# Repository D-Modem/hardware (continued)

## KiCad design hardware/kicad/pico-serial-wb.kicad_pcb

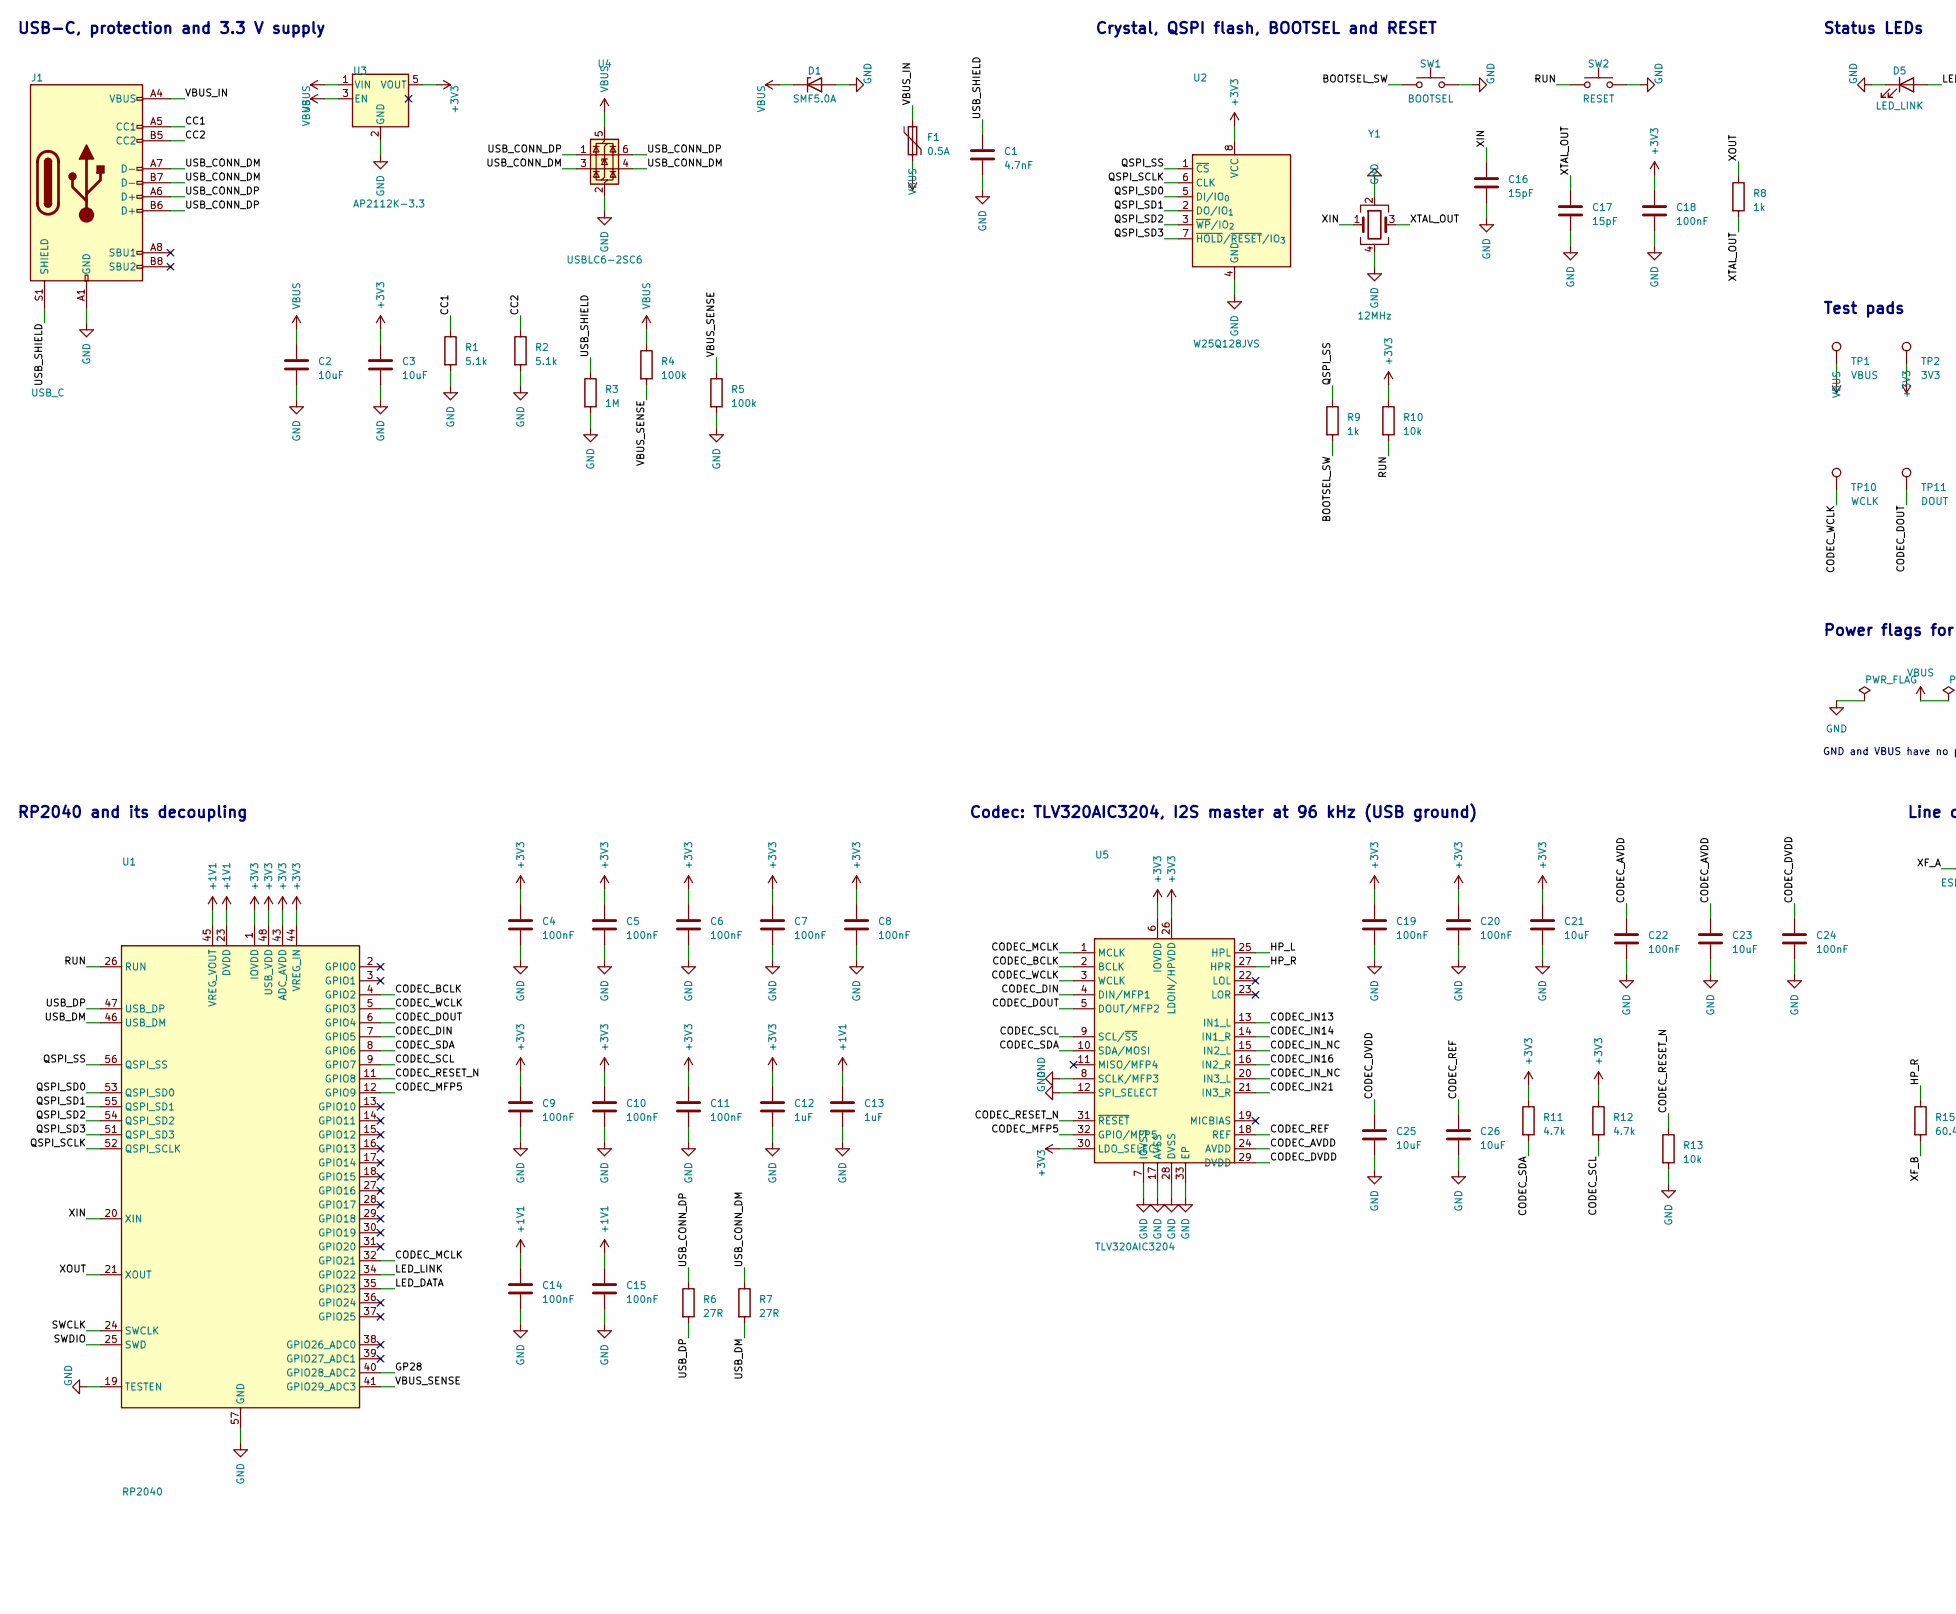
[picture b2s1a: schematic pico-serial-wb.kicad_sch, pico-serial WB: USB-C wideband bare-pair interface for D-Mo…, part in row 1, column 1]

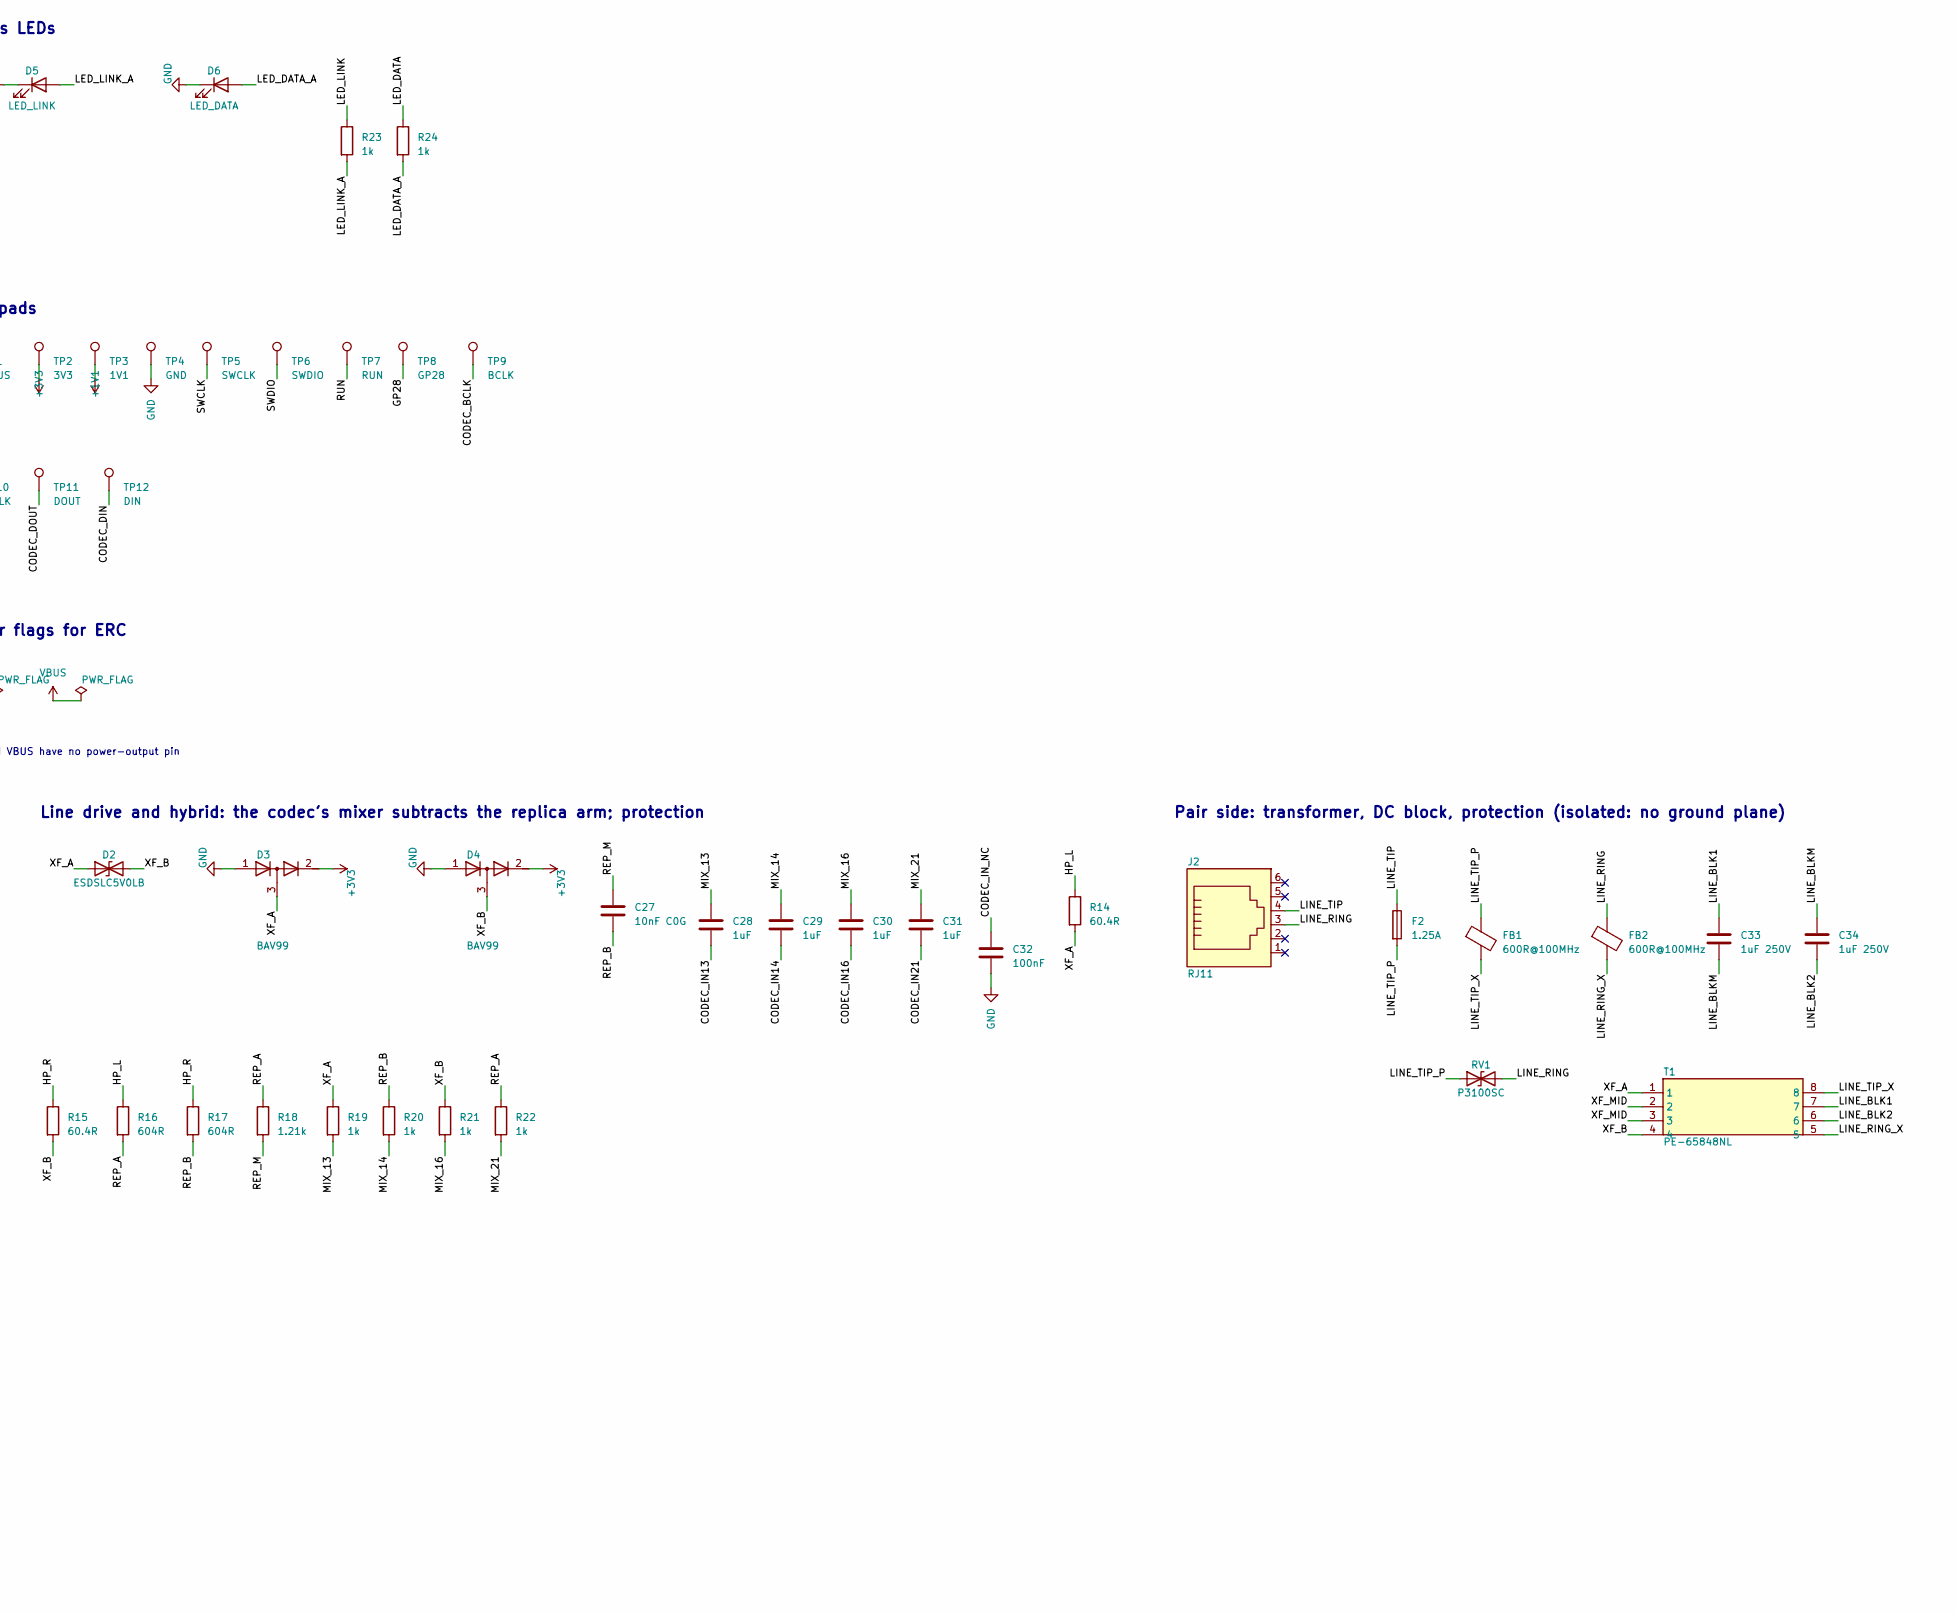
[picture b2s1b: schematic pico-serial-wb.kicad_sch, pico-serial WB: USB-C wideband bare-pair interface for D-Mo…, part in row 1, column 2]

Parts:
C1: 4.7nF; C_0402_1005Metric; LCSC C1538
C2, C3, C21, C23, C25, C26: 10uF; C_0603_1608Metric; LCSC C19702
C4, C5, C6, C7, C8, C9, C10, C11, C14, C15, C18, C19, C20, C22, C24, C32: 100nF; C_0402_1005Metric; LCSC C1525
C12, C13, C28, C29, C30, C31: 1uF; C_0402_1005Metric; LCSC C52923
C16, C17: 15pF; C_0402_1005Metric; LCSC C1548
C27: 10nF C0G; C_0805_2012Metric; LCSC C2971995
C33, C34: 1uF 250V; C_1812_4532Metric; LCSC C381468
D1: SMF5.0A; D_SOD-123F; LCSC C151296
D2: ESDSLC5V0LB; D_0402_1005Metric; LCSC C2762104
D3, D4: BAV99; SOT-23; LCSC C2500
D5: LED_LINK; LED_0603_1608Metric; LCSC C2286
D6: LED_DATA; LED_0603_1608Metric; LCSC C2286
F1: 0.5A; Fuse_1206_3216Metric; LCSC C163512
F2: 1.25A; Fuse_Littelfuse_0461; LCSC C99554
FB1, FB2: 600R@100MHz; L_0603_1608Metric; LCSC C19330
J1: USB_C; USB_C_Receptacle_HRO_TYPE-C-31-M-12; LCSC C165948
J2: RJ11; RJ11_Ckmtw_R-RJ11R06P-A800; LCSC C189750
R1, R2: 5.1k; R_0402_1005Metric; LCSC C25905
R3: 1M; R_0402_1005Metric; LCSC C26083
R4, R5: 100k; R_0402_1005Metric; LCSC C25741
R6, R7: 27R; R_0402_1005Metric; LCSC C25100
R8, R9, R19, R20, R21, R22, R23, R24: 1k; R_0402_1005Metric; LCSC C11702
R10, R13: 10k; R_0402_1005Metric; LCSC C25744
R11, R12: 4.7k; R_0402_1005Metric; LCSC C25900
R14, R15: 60.4R; R_0603_1608Metric; LCSC C2933247
R16, R17: 604R; R_0603_1608Metric; LCSC C32183
R18: 1.21k; R_0603_1608Metric; LCSC C22835
RV1: P3100SC; D_SMB; LCSC C151191
SW1: BOOTSEL; SW_SPST_TS-1088-xR020; LCSC C720477
SW2: RESET; SW_SPST_TS-1088-xR020; LCSC C720477
T1: PE-65848NL; Pulse_PE-65848; LCSC C7261159
TP1: VBUS; TestPoint_Pad_D1.0mm
TP2: 3V3; TestPoint_Pad_D1.0mm
TP3: 1V1; TestPoint_Pad_D1.0mm
TP4: GND; TestPoint_Pad_D1.0mm
TP5: SWCLK; TestPoint_Pad_D1.0mm
TP6: SWDIO; TestPoint_Pad_D1.0mm
TP7: RUN; TestPoint_Pad_D1.0mm
TP8: GP28; TestPoint_Pad_D1.0mm
TP9: BCLK; TestPoint_Pad_D1.0mm
TP10: WCLK; TestPoint_Pad_D1.0mm
TP11: DOUT; TestPoint_Pad_D1.0mm
TP12: DIN; TestPoint_Pad_D1.0mm
U1: RP2040; QFN-56-1EP_7x7mm_P0.4mm_EP3.2x3.2mm; LCSC C2040
U2: W25Q128JVS; SOIC-8_5.3x5.3mm_P1.27mm; LCSC C97521
U3: AP2112K-3.3; SOT-23-5; LCSC C51118
U4: USBLC6-2SC6; SOT-23-6; LCSC C7519
U5: TLV320AIC3204; QFN-32-1EP_5x5mm_P0.5mm_EP3.45x3.45mm; LCSC C24109
Y1: 12MHz; Crystal_SMD_3225-4Pin_3.2x2.5mm; LCSC C20625731

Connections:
+1V1: C13.1, C14.1, C15.1, TP3.1, U1.23 (DVDD), U1.45 (VREG_VOUT), U1.50 (DVDD)
+3V3: C3.1, C4.1, C5.1, C6.1, C7.1, C8.1, C9.1, C10.1, C11.1, C12.1, C18.1, C19.1, C20.1, C21.1, D3.2 (K), D4.2 (K), R10.1, R11.1, R12.1, TP2.1, U1.1 (IOVDD), U1.10 (IOVDD), U1.22 (IOVDD), U1.33 (IOVDD), U1.42 (IOVDD), U1.43 (ADC_AVDD), U1.44 (VREG_IN), U1.48 (USB_VDD), U1.49 (IOVDD), U2.8 (VCC), U3.5 (VOUT), U5.6 (IOVDD), U5.26 (LDOIN/HPVDD), U5.30 (LDO_SELECT)
/BOOTSEL_SW: R9.2, SW1.1
/CC1: J1.A5 (CC1), R1.1
/CC2: J1.B5 (CC2), R2.1
/CODEC_AVDD: C22.1, C23.1, U5.24 (AVDD)
/CODEC_BCLK: TP9.1, U1.4 (GPIO2), U5.2 (BCLK)
/CODEC_DIN: TP12.1, U1.7 (GPIO5), U5.4 (DIN/MFP1)
/CODEC_DOUT: TP11.1, U1.6 (GPIO4), U5.5 (DOUT/MFP2)
/CODEC_DVDD: C24.1, C25.1, U5.29 (DVDD)
/CODEC_IN13: C28.2, U5.13 (IN1_L)
/CODEC_IN14: C29.2, U5.14 (IN1_R)
/CODEC_IN16: C30.2, U5.16 (IN2_R)
/CODEC_IN21: C31.2, U5.21 (IN3_R)
/CODEC_IN_NC: C32.1, U5.15 (IN2_L), U5.20 (IN3_L)
/CODEC_MCLK: U1.32 (GPIO21), U5.1 (MCLK)
/CODEC_MFP5: U1.12 (GPIO9), U5.32 (GPIO/MFP5)
/CODEC_REF: C26.1, U5.18 (REF)
/CODEC_RESET_N: R13.1, U1.11 (GPIO8), U5.31 (~RESET)
/CODEC_SCL: R12.2, U1.9 (GPIO7), U5.9 (SCL/~SS)
/CODEC_SDA: R11.2, U1.8 (GPIO6), U5.10 (SDA/MOSI)
/CODEC_WCLK: TP10.1, U1.5 (GPIO3), U5.3 (WCLK)
/GP28: TP8.1, U1.40 (GPIO28_ADC2)
/HP_L: R14.1, R16.1, U5.25 (HPL)
/HP_R: R15.1, R17.1, U5.27 (HPR)
/LED_DATA: R24.1, U1.35 (GPIO23)
/LED_DATA_A: D6.2 (A), R24.2
/LED_LINK: R23.1, U1.34 (GPIO22)
/LED_LINK_A: D5.2 (A), R23.2
/LINE_BLK1: C33.1, T1.7
/LINE_BLK2: C34.2, T1.6
/LINE_BLKM: C33.2, C34.1
/LINE_RING: FB2.1, J2.3, RV1.2 (A2)
/LINE_RING_X: FB2.2, T1.5
/LINE_TIP: F2.1, J2.4
/LINE_TIP_P: F2.2, FB1.1, RV1.1 (A1)
/LINE_TIP_X: FB1.2, T1.8
/MIX_13: C28.1, R19.2
/MIX_14: C29.1, R20.2
/MIX_16: C30.1, R21.2
/MIX_21: C31.1, R22.2
/QSPI_SCLK: U1.52 (QSPI_SCLK), U2.6 (CLK)
/QSPI_SD0: U1.53 (QSPI_SD0), U2.5 (DI/IO_{0})
/QSPI_SD1: U1.55 (QSPI_SD1), U2.2 (DO/IO_{1})
/QSPI_SD2: U1.54 (QSPI_SD2), U2.3 (~WP/IO_{2})
/QSPI_SD3: U1.51 (QSPI_SD3), U2.7 (~HOLD/~RESET/IO_{3})
/QSPI_SS: R9.1, U1.56 (QSPI_SS), U2.1 (~CS)
/REP_A: R16.2, R18.1, R22.1
/REP_B: C27.2, R17.2, R20.1
/REP_M: C27.1, R18.2
/RUN: R10.2, SW2.1, TP7.1, U1.26 (RUN)
/SWCLK: TP5.1, U1.24 (SWCLK)
/SWDIO: TP6.1, U1.25 (SWD)
/USB_CONN_DM: J1.A7 (D-), J1.B7 (D-), R7.1, U4.3 (I/O2), U4.4 (I/O2)
/USB_CONN_DP: J1.A6 (D+), J1.B6 (D+), R6.1, U4.1 (I/O1), U4.6 (I/O1)
/USB_DM: R7.2, U1.46 (USB_DM)
/USB_DP: R6.2, U1.47 (USB_DP)
/USB_SHIELD: C1.1, J1.S1 (SHIELD), R3.1
/VBUS_IN: F1.1, J1.A4 (VBUS), J1.A9 (VBUS), J1.B4 (VBUS), J1.B9 (VBUS)
/VBUS_SENSE: R4.2, R5.1, U1.41 (GPIO29_ADC3)
/XF_A: D2.1 (A1), D3.3 (common), R14.2, R19.1, T1.1
/XF_B: D2.2 (A2), D4.3 (common), R15.2, R21.1, T1.4
/XF_MID: T1.2, T1.3
/XIN: C16.1, U1.20 (XIN), Y1.1
/XOUT: R8.1, U1.21 (XOUT)
/XTAL_OUT: C17.1, R8.2, Y1.3
GND: C1.2, C2.2, C3.2, C4.2, C5.2, C6.2, C7.2, C8.2, C9.2, C10.2, C11.2, C12.2, C13.2, C14.2, C15.2, C16.2, C17.2, C18.2, C19.2, C20.2, C21.2, C22.2, C23.2, C24.2, C25.2, C26.2, C32.2, D1.2 (A), D3.1 (A), D4.1 (A), D5.1 (K), D6.1 (K), J1.A1 (GND), J1.A12 (GND), J1.B1 (GND), J1.B12 (GND), R1.2, R2.2, R3.2, R5.2, R13.2, SW1.2, SW2.2, TP4.1, U1.19 (TESTEN), U1.57 (GND), U2.4 (GND), U3.2 (GND), U4.2 (GND), U5.7 (IOVSS), U5.8 (SCLK/MFP3), U5.12 (SPI_SELECT), U5.17 (AVSS), U5.28 (DVSS), U5.33 (EP), Y1.2, Y1.4
VBUS: C2.1, D1.1 (K), F1.2, R4.1, TP1.1, U3.1 (VIN), U3.3 (EN), U4.5 (VBUS)

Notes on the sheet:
GND and VBUS have no power-output pin
USB-C, protection and 3.3 V supply
Crystal, QSPI flash, BOOTSEL and RESET
Status LEDs
Test pads
Power flags for ERC
RP2040 and its decoupling
Codec: TLV320AIC3204, I2S master at 96 kHz (USB ground)
Line drive and hybrid: the codec's mixer subtracts the replica arm; protection
Pair side: transformer, DC block, protection (isolated: no ground plane)
Generated by hardware/kicad/build_schematic.py from hardware/netlist/build_netlist.py. Edit the netlist script and regenerate; hand edits here are lost.

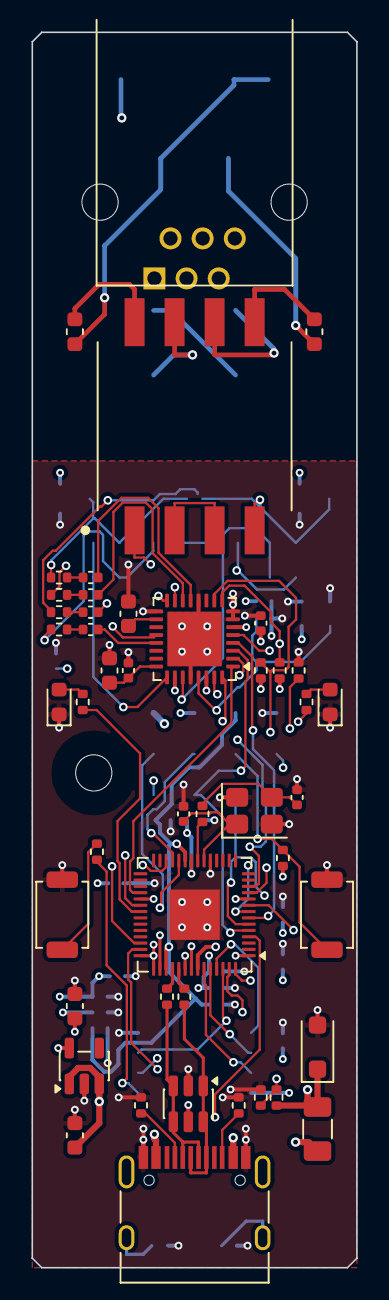
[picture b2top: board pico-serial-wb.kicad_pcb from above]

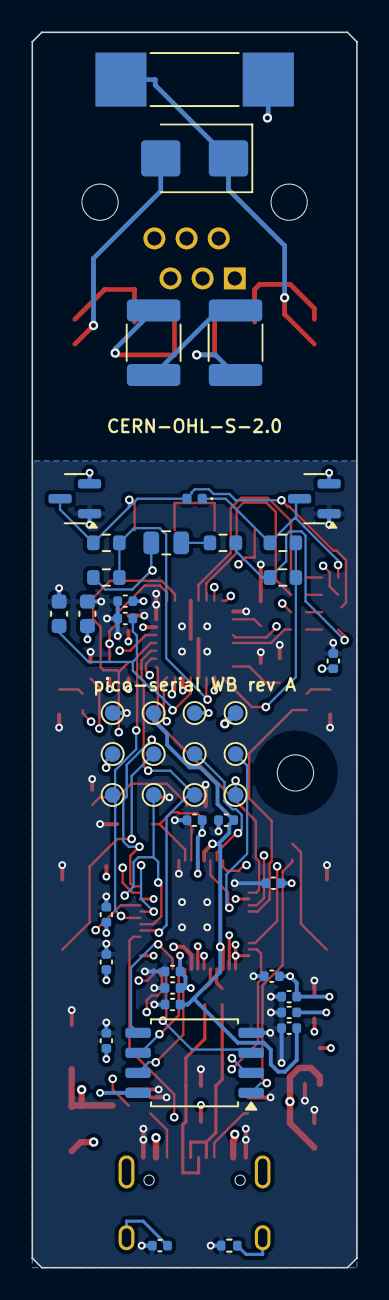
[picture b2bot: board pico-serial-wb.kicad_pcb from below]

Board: 4 copper layers, 20.6 x 78.4 mm, 93 parts (46 on the bottom side), 68 nets.

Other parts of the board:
H1: M2 screw; MountingHole_M2

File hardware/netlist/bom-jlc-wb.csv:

Comment,Designator,Footprint,LCSC Part #
4.7nF,"C1",C_0402_1005Metric,C1538
10uF,"C2,C3,C21,C23,C25,C26",C_0603_1608Metric,C19702
100nF,"C4,C5,C6,C7,C8,C9,C10,C11,C14,C15,C18,C19,C20,C22,C24,C32",C_0402_1005Metric,C1525
1uF,"C12,C13,C28,C29,C30,C31",C_0402_1005Metric,C52923
15pF,"C16,C17",C_0402_1005Metric,C1548
10nF C0G,"C27",C_0805_2012Metric,C2971995
1uF 250V,"C33,C34",C_1812_4532Metric,C381468
SMF5.0A,"D1",D_SOD-123F,C151296
ESDSLC5V0LB,"D2",D_0402_1005Metric,C2762104
BAV99,"D3,D4",SOT-23,C2500
LED_LINK,"D5",LED_0603_1608Metric,C2286
LED_DATA,"D6",LED_0603_1608Metric,C2286
0.5A,"F1",Fuse_1206_3216Metric,C163512
1.25A,"F2",Fuse_Littelfuse_0461,C99554
600R@100MHz,"FB1,FB2",L_0603_1608Metric,C19330
USB_C,"J1",USB_C_Receptacle_HRO_TYPE-C-31-M-12,C165948
5.1k,"R1,R2",R_0402_1005Metric,C25905
1M,"R3",R_0402_1005Metric,C26083
100k,"R4,R5",R_0402_1005Metric,C25741
27R,"R6,R7",R_0402_1005Metric,C25100
1k,"R8,R9,R19,R20,R21,R22,R23,R24",R_0402_1005Metric,C11702
10k,"R10,R13",R_0402_1005Metric,C25744
4.7k,"R11,R12",R_0402_1005Metric,C25900
60.4R,"R14,R15",R_0603_1608Metric,C2933247
604R,"R16,R17",R_0603_1608Metric,C32183
1.21k,"R18",R_0603_1608Metric,C22835
P3100SC,"RV1",D_SMB,C151191
BOOTSEL,"SW1",SW_SPST_TS-1088-xR020,C720477
RESET,"SW2",SW_SPST_TS-1088-xR020,C720477
PE-65848NL,"T1",Pulse_PE-65848,C7261159
RP2040,"U1",QFN-56-1EP_7x7mm_P0.4mm_EP3.2x3.2mm,C2040
W25Q128JVS,"U2",SOIC-8_5.3x5.3mm_P1.27mm,C97521
AP2112K-3.3,"U3",SOT-23-5,C51118
USBLC6-2SC6,"U4",SOT-23-6,C7519
TLV320AIC3204,"U5",QFN-32-1EP_5x5mm_P0.5mm_EP3.45x3.45mm,C24109
12MHz,"Y1",Crystal_SMD_3225-4Pin_3.2x2.5mm,C20625731

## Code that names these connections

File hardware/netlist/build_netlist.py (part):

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P, PI, PO, I, O, B, NC = "passive", "power_in", "power_out", "input", "output", "bidirectional", "no_connect"

RP2040 = {
    "1": ("IOVDD", PI), "2": ("GPIO0", B), "3": ("GPIO1", B), "4": ("GPIO2", B), "5": ("GPIO3", B),
    "6": ("GPIO4", B), "7": ("GPIO5", B), "8": ("GPIO6", B), "9": ("GPIO7", B), "10": ("IOVDD", P),
    "11": ("GPIO8", B), "12": ("GPIO9", B), "13": ("GPIO10", B), "14": ("GPIO11", B), "15": ("GPIO12", B),
    "16": ("GPIO13", B), "17": ("GPIO14", B), "18": ("GPIO15", B), "19": ("TESTEN", I), "20": ("XIN", I),
    "21": ("XOUT", O), "22": ("IOVDD", P), "23": ("DVDD", PI), "24": ("SWCLK", I), "25": ("SWD", B),
    "26": ("RUN", I), "27": ("GPIO16", B), "28": ("GPIO17", B), "29": ("GPIO18", B), "30": ("GPIO19", B),
    "31": ("GPIO20", B), "32": ("GPIO21", B), "33": ("IOVDD", P), "34": ("GPIO22", B), "35": ("GPIO23", B),
    "36": ("GPIO24", B), "37": ("GPIO25", B), "38": ("GPIO26_ADC0", B), "39": ("GPIO27_ADC1", B),
    "40": ("GPIO28_ADC2", B), "41": ("GPIO29_ADC3", B), "42": ("IOVDD", P), "43": ("ADC_AVDD", PI),
    "44": ("VREG_IN", PI), "45": ("VREG_VOUT", PO), "46": ("USB_DM", B), "47": ("USB_DP", B),
    "48": ("USB_VDD", PI), "49": ("IOVDD", P), "50": ("DVDD", P), "51": ("QSPI_SD3", B),
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# Raspberry Pi RM2 (RMC20452T), datasheet Table 2. GND pins are passive in
# KiCad terms; VDDIO and Vin are power inputs.
RM2 = {"1": ("GND", PI), "2": ("NC", NC), "3": ("SCLK", I), "4": ("GND", PI), "5": ("DATA_IN", I),
       "6": ("DATA_OUT", O), "7": ("GND", PI), "8": ("GPIO0", B), "9": ("CS", I), "10": ("~{IRQ}", O),
       "11": ("GND", PI), "12": ("WL_ON", I), "13": ("BT_ON", I), "14": ("VDDIO", PI), "15": ("GND", PI),
       "16": ("VIN", PI), "17": ("GPIO2", B), "18": ("GPIO1", B), "19": ("NC", NC), "20": ("NC", NC),
       "21": ("GND", PI)}
# Skyworks Si3056 Global Serial Interface DAA, system side (datasheet rev 1.03,
# Table 24) and its Si3018/19 line side (Table 25; the two have the same pins). Line-side pins are all
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        conn(net, (J2, db), (UA, a), (UB, b))
    conn(GND, (J2, "7"))
    conn("DB25_FG", (J2, "1"))
    passive("R", "0R", "DB25_FG", GND, "frame ground to GND; leave off to float pin 1")
    nc(J2, *[str(n) for n in range(1, 26) if str(n) not in {"1", "2", "3", "4", "5", "6", "7", "8", "20", "22"}])

    # --- §4.6 GPIO map ------------------------------------------------------------
    GPIO = {  # GPIO: (net, chip pin)
        0: ("A_TX", (UA, "24")),      # UART0 TX set A -> T1IN -> pin 3
        1: ("A_RX", (UA, "21")),      # UART0 RX set A <- R1OUT <- pin 2
        2: ("A_CTS", (UA, "20")),     # UART0 CTS set A <- R2OUT <- pin 4 (computer's RTS)
        3: ("A_RTS", (UA, "23")),     # UART0 RTS set A -> T2IN -> pin 5 (CTS to computer)
        4: ("A_DSR", (UA, "22")),     # T3IN -> pin 6
        5: ("A_DCD", (UA, "19")),     # T4IN -> pin 8
        6: ("A_RI", (UA, "17")),      # T5IN -> pin 22
        7: ("A_DTR", (UA, "18")),     # R3OUT <- pin 20
        8: ("B_DTR", (UB, "12")),     # DIN3 -> pin 20
        9: ("B_DSR", (UB, "17")),     # ROUT3 <- pin 6
        10: ("B_DCD", (UB, "16")),    # ROUT4 <- pin 8
        11: ("B_RI", (UB, "15")),     # ROUT5 <- pin 22
        12: ("B_TX", (UB, "14")),     # UART0 TX set B -> DIN1 -> pin 2
        13: ("B_RX", (UB, "19")),     # UART0 RX set B <- ROUT1 <- pin 3
        14: ("B_CTS", (UB, "18")),    # UART0 CTS set B <- ROUT2 <- pin 5
        15: ("B_RTS", (UB, "13")),    # UART0 RTS set B -> DIN2 -> pin 4
        16: ("A_SHDN_N", (UA, "14")), # chip A ~SHUTDOWN, pulled low
        17: ("B_FORCEOFF_N", (UB, "22")),  # chip B ~FORCEOFF, pulled low
        19: ("A_R1OUTB", (UA, "16")), # chip A always-on non-inverting R1 (pin 2)
        20: ("A_STATUS", (UA, "15")), # chip A STATUS, valid in shutdown
        21: ("B_INVALID", (UB, "21")),# chip B INVALID, valid in shutdown
    }
    for g, (net, node) in GPIO.items():
        conn(net, (U1, GPIO_PIN[g]), node)
    # GP18 drives chip A ONLINE and chip B FORCEON together
    conn("RS_FORCEON", (U1, GPIO_PIN[18]), (UA, "13"), (UB, "23"))
    block("rsa")
    passive("R", "100k", "A_SHDN_N", GND, "chip A off until firmware decides")
    block("rsb")
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    passive("R", "100k", "RS_FORCEON", GND, "auto power-down on until firmware decides")
    nc(UB, "20")  # ROUT2B unused (INVALID covers detection)
if not W:
    conn("VBUS_SENSE", (U1, GPIO_PIN[29]))   # W: on the RM2's GPIO0 instead (SPEC-W §3.3)

if W:
    # --- SPEC-W §3.1 RM2 radio, wired exactly like Pico W ------------------------
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              desc="Raspberry Pi RM2 (SC1169), CYW43439; DigiKey 2648-SC1169CT-ND, not at LCSC")
    conn(GND, *[(RM, p) for p in ("1", "4", "7", "11", "15", "21")])
    nc(RM, "2", "19", "20")
    conn("WL_ON", (U1, GPIO_PIN[23]), (RM, "12"), (RM, "13"))   # Wi-Fi and Bluetooth on together
    conn("WL_D", (U1, GPIO_PIN[24]), (RM, "5"))                 # gSPI data in, shared pin
    conn("WL_CS", (U1, GPIO_PIN[25]), (RM, "9"))
    conn("WL_CLK", (U1, GPIO_PIN[29]), (RM, "3"))
    conn(V33, (RM, "14"), (RM, "16"))
    conn("VBUS_SENSE", (RM, "8"))                               # RM2 GPIO0: VBUS present

if LINE:
    # --- SPEC-L §3: the telephone line, Si3056 + Si3019 DAA (datasheet Figure 17) ---
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    UC = wp("U", "codec", ref="U5", pins=AIC3204)
    conn(V33, (UC, "6"), (UC, "26"), (UC, "30"))           # IOVDD, LDOIN/HPVDD, LDO_SELECT (D-LDO on)
    conn(GND, (UC, "7"), (UC, "17"), (UC, "28"), (UC, "33"), (UC, "12"), (UC, "8"))   # grounds; I2C mode; MFP3 unused
    for pin, net, g in (("1", "CODEC_MCLK", 21), ("2", "CODEC_BCLK", 2), ("3", "CODEC_WCLK", 3),
                        ("5", "CODEC_DOUT", 4), ("4", "CODEC_DIN", 5), ("10", "CODEC_SDA", 6),
                        ("9", "CODEC_SCL", 7), ("31", "CODEC_RESET_N", 8), ("32", "CODEC_MFP5", 9)):
        conn(net, (U1, GPIO_PIN[g]), (UC, pin))            # I2S on GP2-5 (one PIO block), I2C1 on GP6/7
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    wp("R", "1k21", "REP_A", "REP_M")                       # Zb: the cable's R and C, times ten
    wp("C", "10nF C0G", "REP_M", "REP_B")
    # each mixer input through 1k (current limit for the clamps) and 1 uF (the codec wants AC coupling)
    for node, pin, what in (("XF_A", "13", "IN1_L: P, line +"), ("REP_B", "14", "IN1_R: P, replica -"),
                            ("XF_B", "16", "IN2_R: M, line -"), ("REP_A", "21", "IN3_R: M, replica +")):
        mid = f"MIX_{pin}"
        passive("R", "1k", node, mid, f"{what}: input series R")
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    # SPEC-W §4.5 pairing button, reached through a pinhole in the hood
    SW3 = part("SW", "PAIR", SW, "Button_Switch_SMD:SW_SPST_TS-1088-xR020", "C720477",
               desc="XUNPU TS-1088-AR02016, pairing")
    conn("PAIR_BTN", (U1, GPIO_PIN[28]), (SW3, "1")); conn(GND, (SW3, "2"))


# ===========================================================================
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
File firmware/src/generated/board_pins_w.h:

/*
 * SPDX-License-Identifier: AGPL-3.0-only
 * Copyright (C) 2026 D-Modem Authors
 */
// Generated by hardware/netlist/build_netlist.py from the board's nets. Do not edit.
#pragma once

#define PIN_A_TX              0   // GP0
#define PIN_A_RX              1   // GP1
#define PIN_A_CTS             2   // GP2
#define PIN_A_RTS             3   // GP3
#define PIN_A_DSR             4   // GP4
#define PIN_A_DCD             5   // GP5
#define PIN_A_RI              6   // GP6
#define PIN_A_DTR             7   // GP7
#define PIN_B_DTR             8   // GP8
#define PIN_B_DSR             9   // GP9
#define PIN_B_DCD            10   // GP10
#define PIN_B_RI             11   // GP11
#define PIN_B_TX             12   // GP12
#define PIN_B_RX             13   // GP13
#define PIN_B_CTS            14   // GP14
#define PIN_B_RTS            15   // GP15
#define PIN_A_SHDN_N         16   // GP16
#define PIN_B_FORCEOFF_N     17   // GP17
#define PIN_RS_FORCEON       18   // GP18
#define PIN_A_R1OUTB         19   // GP19
#define PIN_A_STATUS         20   // GP20
#define PIN_B_INVALID        21   // GP21
#define PIN_LED_BT           22   // GP22
#define PIN_WL_ON            23   // GP23
#define PIN_WL_D             24   // GP24
#define PIN_WL_CS            25   // GP25
#define PIN_LED_TR           26   // GP26
#define PIN_LED_CD           27   // GP27
#define PIN_PAIR_BTN         28   // GP28
#define PIN_WL_CLK           29   // GP29

// RM2 (CYW43439) GPIOs: cyw43_arch_gpio_get/put
#define WLGPIO_LED_RD          1   // RM2 pin 18
#define WLGPIO_LED_SD          2   // RM2 pin 17
#define WLGPIO_VBUS_SENSE      0   // RM2 pin 8

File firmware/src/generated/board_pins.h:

/*
 * SPDX-License-Identifier: AGPL-3.0-only
 * Copyright (C) 2026 D-Modem Authors
 */
// Generated by hardware/netlist/build_netlist.py from the board's nets. Do not edit.
#pragma once

#define PIN_A_TX              0   // GP0
#define PIN_A_RX              1   // GP1
#define PIN_A_CTS             2   // GP2
#define PIN_A_RTS             3   // GP3
#define PIN_A_DSR             4   // GP4
#define PIN_A_DCD             5   // GP5
#define PIN_A_RI              6   // GP6
#define PIN_A_DTR             7   // GP7
#define PIN_B_DTR             8   // GP8
#define PIN_B_DSR             9   // GP9
#define PIN_B_DCD            10   // GP10
#define PIN_B_RI             11   // GP11
#define PIN_B_TX             12   // GP12
#define PIN_B_RX             13   // GP13
#define PIN_B_CTS            14   // GP14
#define PIN_B_RTS            15   // GP15
#define PIN_A_SHDN_N         16   // GP16
#define PIN_B_FORCEOFF_N     17   // GP17
#define PIN_RS_FORCEON       18   // GP18
#define PIN_A_R1OUTB         19   // GP19
#define PIN_A_STATUS         20   // GP20
#define PIN_B_INVALID        21   // GP21
#define PIN_LED_PWR          22   // GP22
#define PIN_LED_TR           23   // GP23
#define PIN_LED_CD           24   // GP24
#define PIN_LED_SD           25   // GP25
#define PIN_LED_RD           26   // GP26
#define PIN_LED_RI           27   // GP27
#define PIN_GP28             28   // GP28
#define PIN_VBUS_SENSE       29   // GP29

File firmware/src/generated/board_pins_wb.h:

/*
 * SPDX-License-Identifier: AGPL-3.0-only
 * Copyright (C) 2026 D-Modem Authors
 */
// Generated by hardware/netlist/build_netlist.py from the board's nets. Do not edit.
#pragma once

#define PIN_CODEC_BCLK        2   // GP2
#define PIN_CODEC_WCLK        3   // GP3
#define PIN_CODEC_DOUT        4   // GP4
#define PIN_CODEC_DIN         5   // GP5
#define PIN_CODEC_SDA         6   // GP6
#define PIN_CODEC_SCL         7   // GP7
#define PIN_CODEC_RESET_N     8   // GP8
#define PIN_CODEC_MFP5        9   // GP9
#define PIN_CODEC_MCLK       21   // GP21
#define PIN_LED_LINK         22   // GP22
#define PIN_LED_DATA         23   // GP23
#define PIN_GP28             28   // GP28
#define PIN_VBUS_SENSE       29   // GP29
